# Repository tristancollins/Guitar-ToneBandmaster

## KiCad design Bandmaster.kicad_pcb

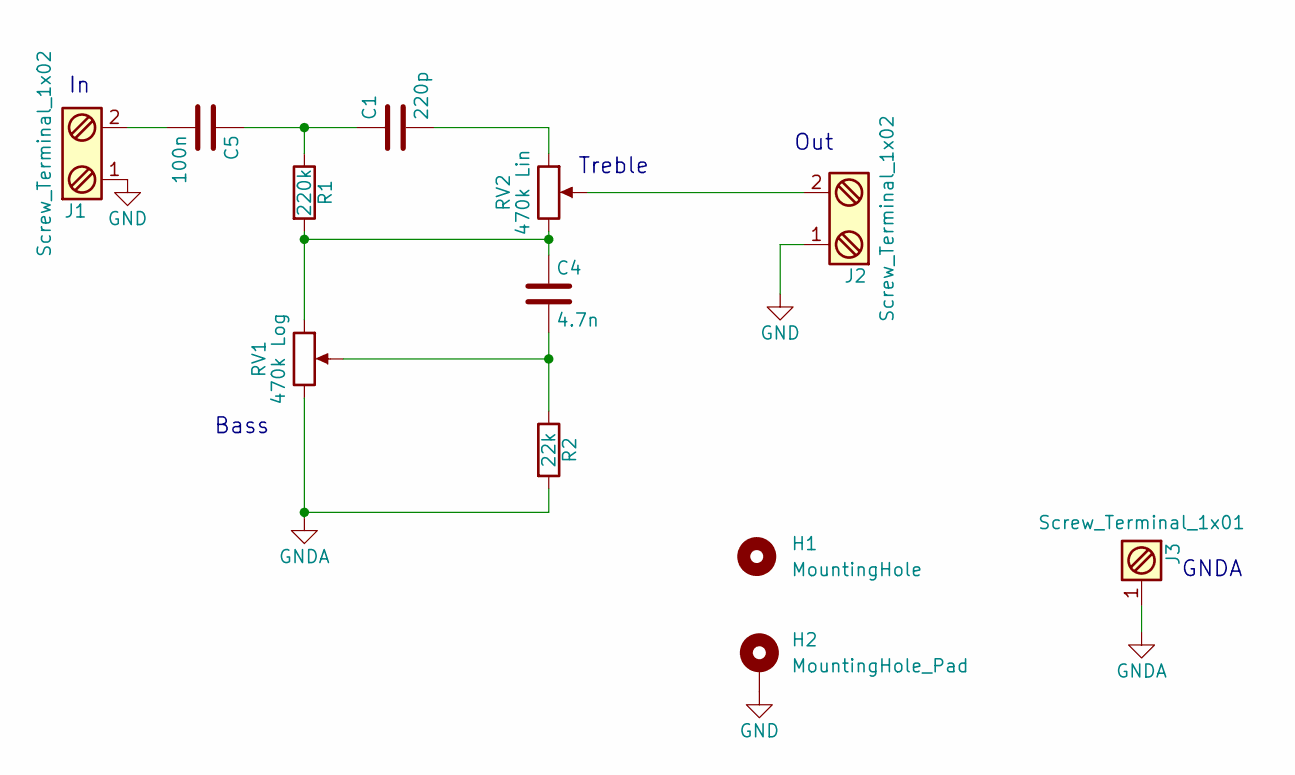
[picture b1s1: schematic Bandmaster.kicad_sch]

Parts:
C1: 220p; C_Disc_D7.5mm_W5.0mm_P7.50mm
C4: 4.7n; C_Axial_L12.0mm_D6.5mm_P15.00mm_Horizontal
C5: 100n; C_Axial_L22.0mm_D9.5mm_P27.50mm_Horizontal
H1: MountingHole; MountingHole_3.2mm_M3
H2: MountingHole_Pad; MountingHole_3.2mm_M3_Pad
J1, J2: Screw_Terminal_1x02; PhoenixContact_MCV_1,5_2-G-5.08_1x02_P5.08mm_Vertical
J3: Screw_Terminal_1x01; SolderWire-0.75sqmm_1x01_D1.25mm_OD2.3mm
R1: 220k; R_Axial_DIN0414_L11.9mm_D4.5mm_P15.24mm_Horizontal
R2: 22k; R_Axial_DIN0414_L11.9mm_D4.5mm_P15.24mm_Horizontal
RV1: 470k Log; PhoenixContact_MCV_1,5_3-G-5.08_1x03_P5.08mm_Vertical; MPN 1729131
RV2: 470k Lin; PhoenixContact_MCV_1,5_3-G-5.08_1x03_P5.08mm_Vertical; MPN 1729131

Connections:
GND: H2.1, J1.1, J2.1
GNDA: J3.1, R2.2, RV1.3
unnamed: C1.1, C5.1, R1.1
unnamed: C1.2, RV2.1
unnamed: C4.1, R1.2, RV1.1, RV2.3
unnamed: C4.2, R2.1, RV1.2
unnamed: C5.2, J1.2
unnamed: J2.2, RV2.2

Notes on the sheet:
Treble
Out
Bass
GNDA

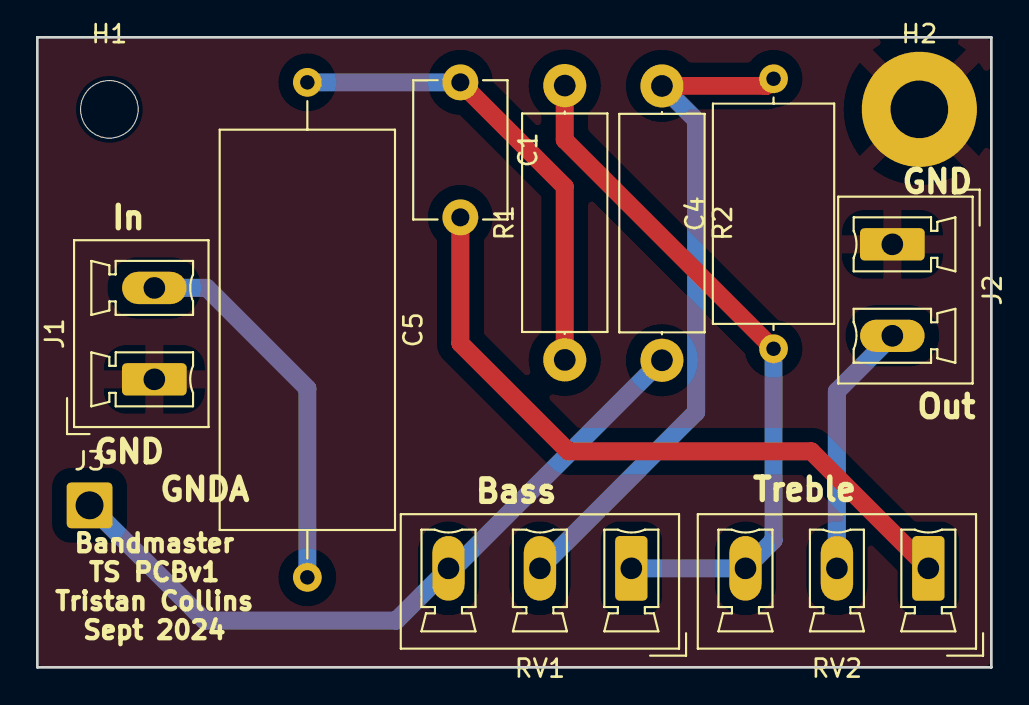
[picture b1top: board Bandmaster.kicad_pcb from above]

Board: 2 copper layers, 53.0 x 35.0 mm, 12 parts (0 on the bottom side), 8 nets.
